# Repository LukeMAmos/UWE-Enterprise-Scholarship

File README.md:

# University of the West of England Enterprise Summer Scholarship 2026

As part of the UWE Enterprise Summer Scholarship 2026, I began research and development into a portable synthesis device which combined both software and hardware elements. Its intention being a device targeted at beginners, to introduce them into musical production. I began by first completing market research on current devices on the market with a similar intention, I then moved onto a design and feedback stage of building and improving the device. 

## Features 

A ESP32 Based synthesiser which can connect via Bluetooth to a JUCE app to control elements of the synths sound. It then used an MPR121 to detect touches on the copper pads and used these to trigger the notes. 

## Project Images

## Built using 
- JUCE Framework 
- C++
- PlatformIO

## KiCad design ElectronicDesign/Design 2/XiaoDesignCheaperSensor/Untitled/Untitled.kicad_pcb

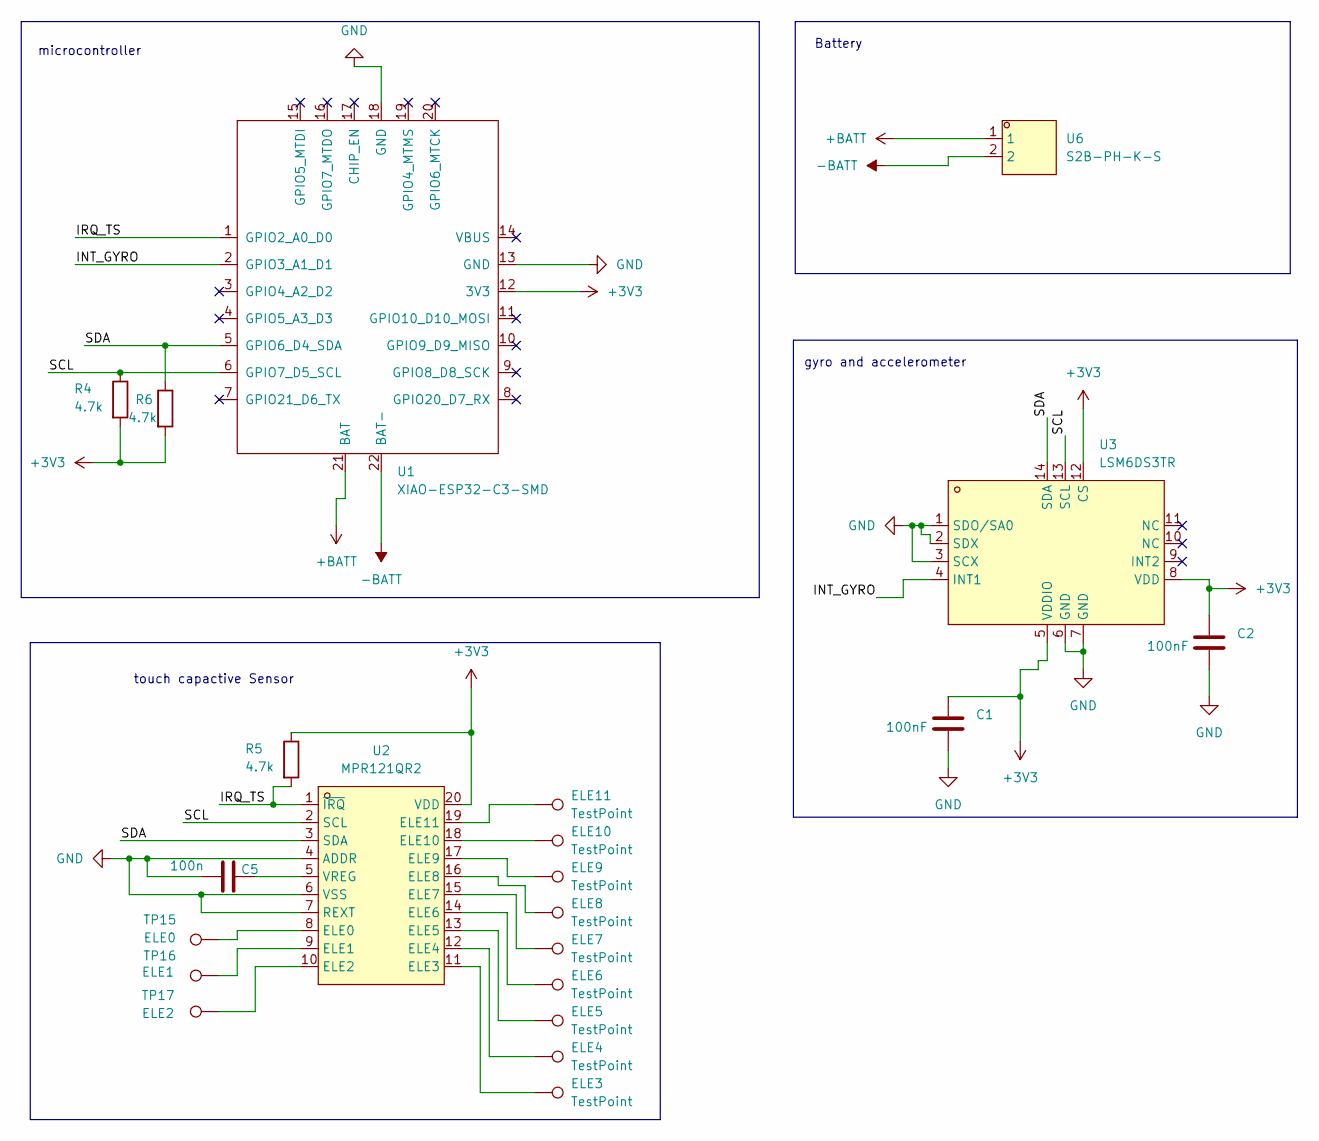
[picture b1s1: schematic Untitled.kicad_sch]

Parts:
C1, C2: 100nF; C_0805_2012Metric
C5: 100n; C_0805_2012Metric; LCSC Part C1711
ELE3, ELE4, ELE5, ELE6, ELE7, ELE8, ELE9, ELE10, ELE11: TestPoint; Untitled
R4, R5, R6: 4.7k; R_0805_2012Metric; LCSC Part C702835
TP15: ELE0; Untitled
TP16: ELE1; Untitled
TP17: ELE2; Untitled
U1: XIAO-ESP32-C3-SMD
U2: MPR121QR2; QFN-20_L3.0-W3.0-P0.40-BL; MPN MPR121QR2; LCSC Part C91322
U3: LSM6DS3TR; LGA-14_L3.0-W2.5-P0.50-TL; MPN LSM6DS3TR; LCSC Part C95230
U6: S2B-PH-K-S; CONN-TH_S2B-PH-K-S-LF-SN; MPN S2B-PH-K-S(LF)(SN); LCSC Part C173752

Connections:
+3V3: C1.2, C2.2, R4.2, R5.1, R6.2, U1.12 (3V3), U2.20 (VDD), U3.5 (VDDIO), U3.8 (VDD), U3.12 (CS)
+BATT: U1.21 (BAT), U6.1
-BATT: U1.22 (BAT-), U6.2
/INT_GYRO: U1.2 (GPIO3_A1_D1), U3.4 (INT1)
/IRQ_TS: R5.2, U1.1 (GPIO2_A0_D0), U2.1 (~IRQ)
/SCL: R4.1, U1.6 (GPIO7_D5_SCL), U2.2 (SCL), U3.13 (SCL)
/SDA: R6.1, U1.5 (GPIO6_D4_SDA), U2.3 (SDA), U3.14 (SDA)
GND: C1.1, C2.1, C5.2, U1.13 (GND), U1.18 (GND), U2.4 (ADDR), U2.6 (VSS), U2.7 (REXT), U3.1 (SDO/SA0), U3.2 (SDX), U3.3 (SCX), U3.6 (GND), U3.7 (GND)
unnamed: TP15.1 (1_1), U2.8 (ELE0)
unnamed: TP16.1 (1_1), U2.9 (ELE1)
unnamed: TP17.1 (1_1), U2.10 (ELE2)
unnamed: ELE3.1 (1_1), U2.11 (ELE3)
unnamed: ELE4.1 (1_1), U2.12 (ELE4)
unnamed: ELE5.1 (1_1), U2.13 (ELE5)
unnamed: ELE6.1 (1_1), U2.14 (ELE6)
unnamed: ELE7.1 (1_1), U2.15 (ELE7)
unnamed: ELE8.1 (1_1), U2.16 (ELE8)
unnamed: ELE9.1 (1_1), U2.17 (ELE9)
unnamed: ELE10.1 (1_1), U2.18 (ELE10)
unnamed: ELE11.1 (1_1), U2.19 (ELE11)
unnamed: C5.1, U2.5 (VREG)

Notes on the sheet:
Battery
gyro and accelerometer
touch capactive Sensor
microcontroller

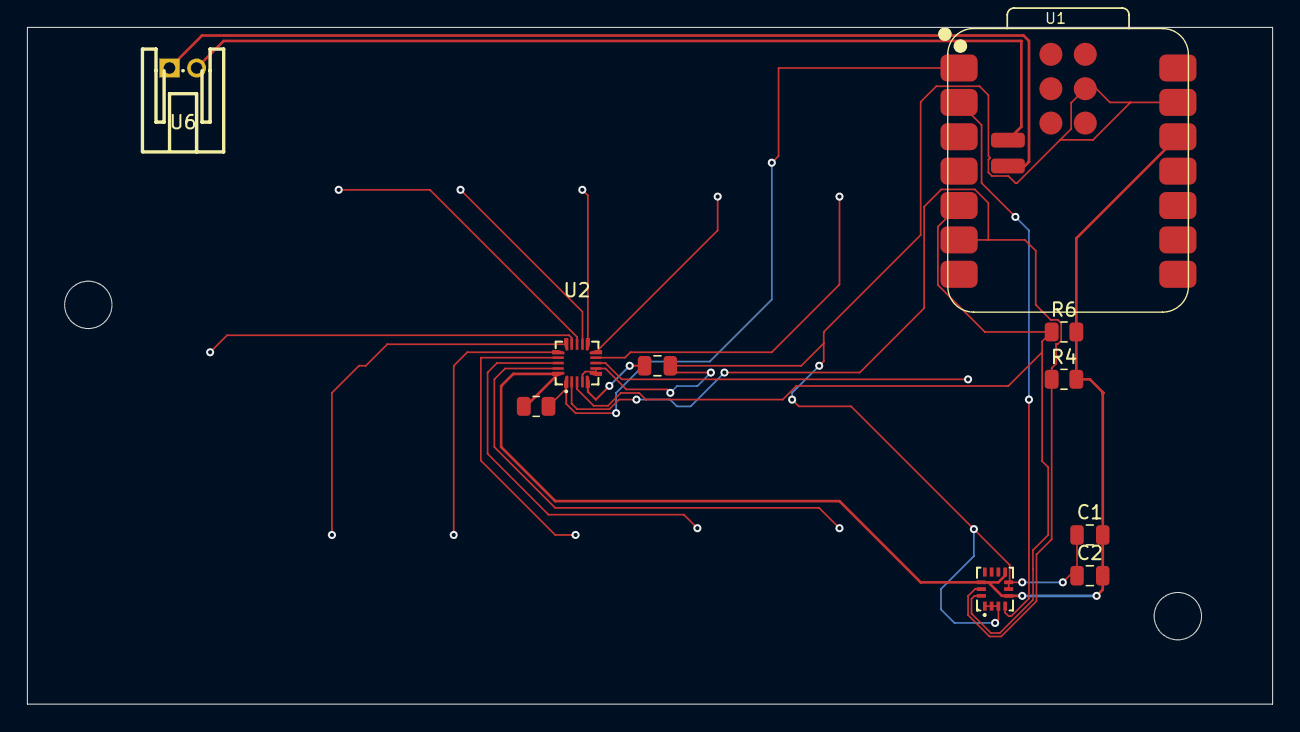
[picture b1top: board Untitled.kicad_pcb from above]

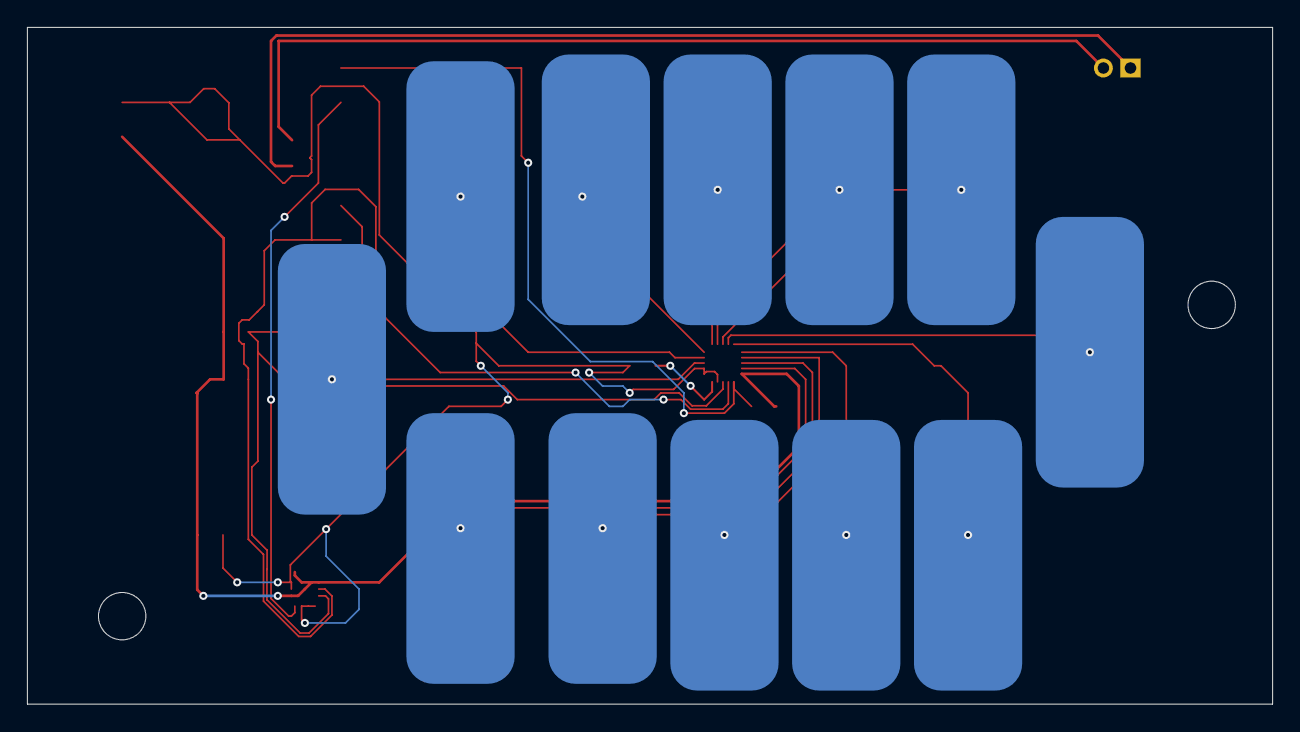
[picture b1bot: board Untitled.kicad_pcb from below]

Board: 2 copper layers, 92.0 x 50.0 mm, 22 parts (12 on the bottom side), 21 nets.

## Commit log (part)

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2026-05-30 Initial Commit
    Initial Documents
2026-05-31 Create README for UWE Enterprise Summer Scholarship 2026
    Add initial README with project details for UWE scholarship.
2026-06-10 Add KiCad ElectronicDesign project files
2026-06-12 Alias to source code
2026-06-12 Source Code update , including Juce application that renders 3d model and has midi synth setup
2026-06-12 Add Builds directory to .gitignore
2026-06-12 Remove Builds
2026-06-14 Update to code outlining the method for re-interpreting midi messages before being sent through to the synth
2026-06-14 Update to code to implement new look and feel component
2026-06-14 New Schematic design with Hall Effect Sensor , Updated program to fit with new method of re-interpreting midi data from the device , Added new exporter of IOS app
2026-06-18 Update to Electronic design with additional design implemented using Xiao microcontroller
2026-06-18 Adding base class to allow for common type in creating a vector of effects
2026-06-18 Update to implementation of base class and vector
2026-06-18 Continued Routing on the PCB Design , implementation of delay effect started and vector method for effects implemented
    Vector method for effects will allow for the user to change the order of the effects using hopefully a draggable component from a previous project
2026-06-18 Draggable component implemented for re ordering effect chain
2026-06-19 Implementation of simplified draggable component
2026-06-19 Updates to draggable component , Re tracing the pcb routing to change the position of the microcontroller
2026-06-19 Update to the routing
2026-06-19 Updated the draggable component constructor and implemented an array of the draggable components
    Name of the effect connected to the draggable component is now passed through in the constructor , an array of the draggable components equal in size to the number of effects in the synth
2026-06-19 Update to wiring and draggable component implementation
2026-06-20 Work continued on the PCB , Update to the synth code , moved effect processing
    Effect processing now in Synth Audio Source reducing the number effect from Voices * numEffects to just NumEffects
2026-06-20 Update to draggable component constructor
    Implement method to choose number of components inside the draggable component , by moving a vector of unique pointers to components into a stored vector inside the draggable component
2026-06-20 Updated schematic with new component
2026-06-24 Multipage folder and update to report document
2026-06-24 Implementing pages view
    Each page is its own component that on a button view state can be switched, pages include , 3D rendering of the device and its movements , choosing synthesis and ordering effects and selecting how th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
2026-06-26 Refactoring to place rending program into its own page to allow for switching between different views
    Re-located the rendering code to a child page of the main component
2026-06-26 Additional Update to previous commit
2026-06-28 Update to code
2026-06-28 Pages built with button
    Button press and page view not yet implemented
